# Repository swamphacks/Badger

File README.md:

# Badger

## QR Code Labels

### Installation

This script requires that Python library `qrcode` and [LibreOffice](https://www.libreoffice.org/download) be installed.

```bash
pip install -r requirements.txt
```

### Usage

Run `python cycle.py` to generate pages of QR codes. Exported PDFs will be saved in `output/`.

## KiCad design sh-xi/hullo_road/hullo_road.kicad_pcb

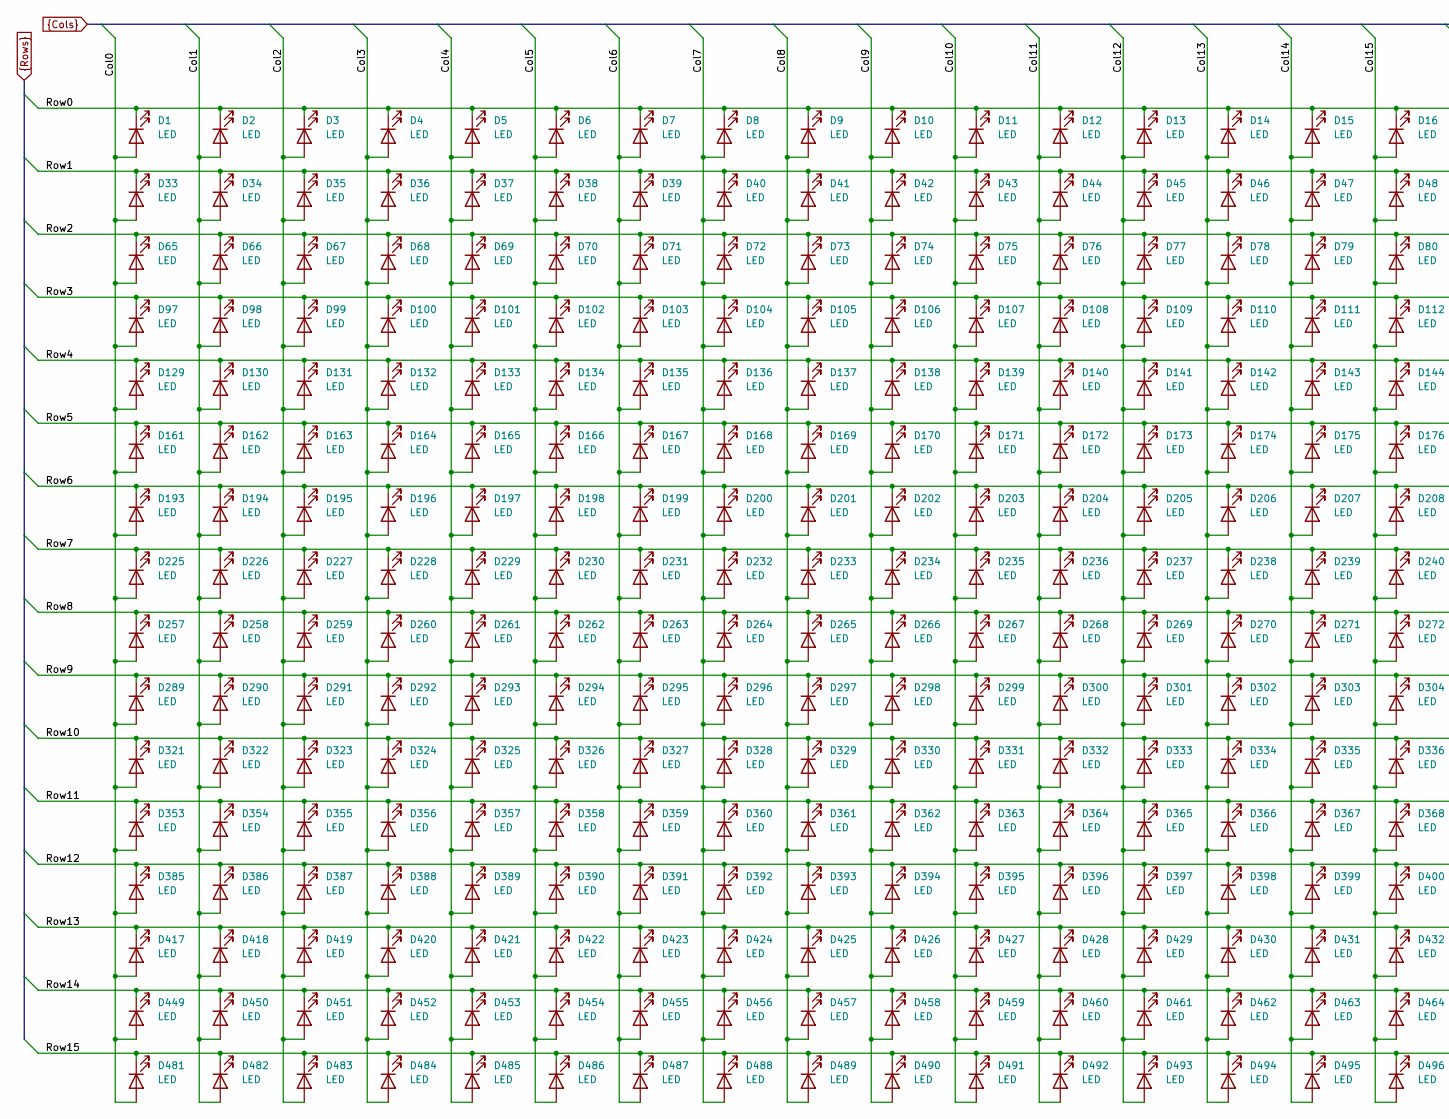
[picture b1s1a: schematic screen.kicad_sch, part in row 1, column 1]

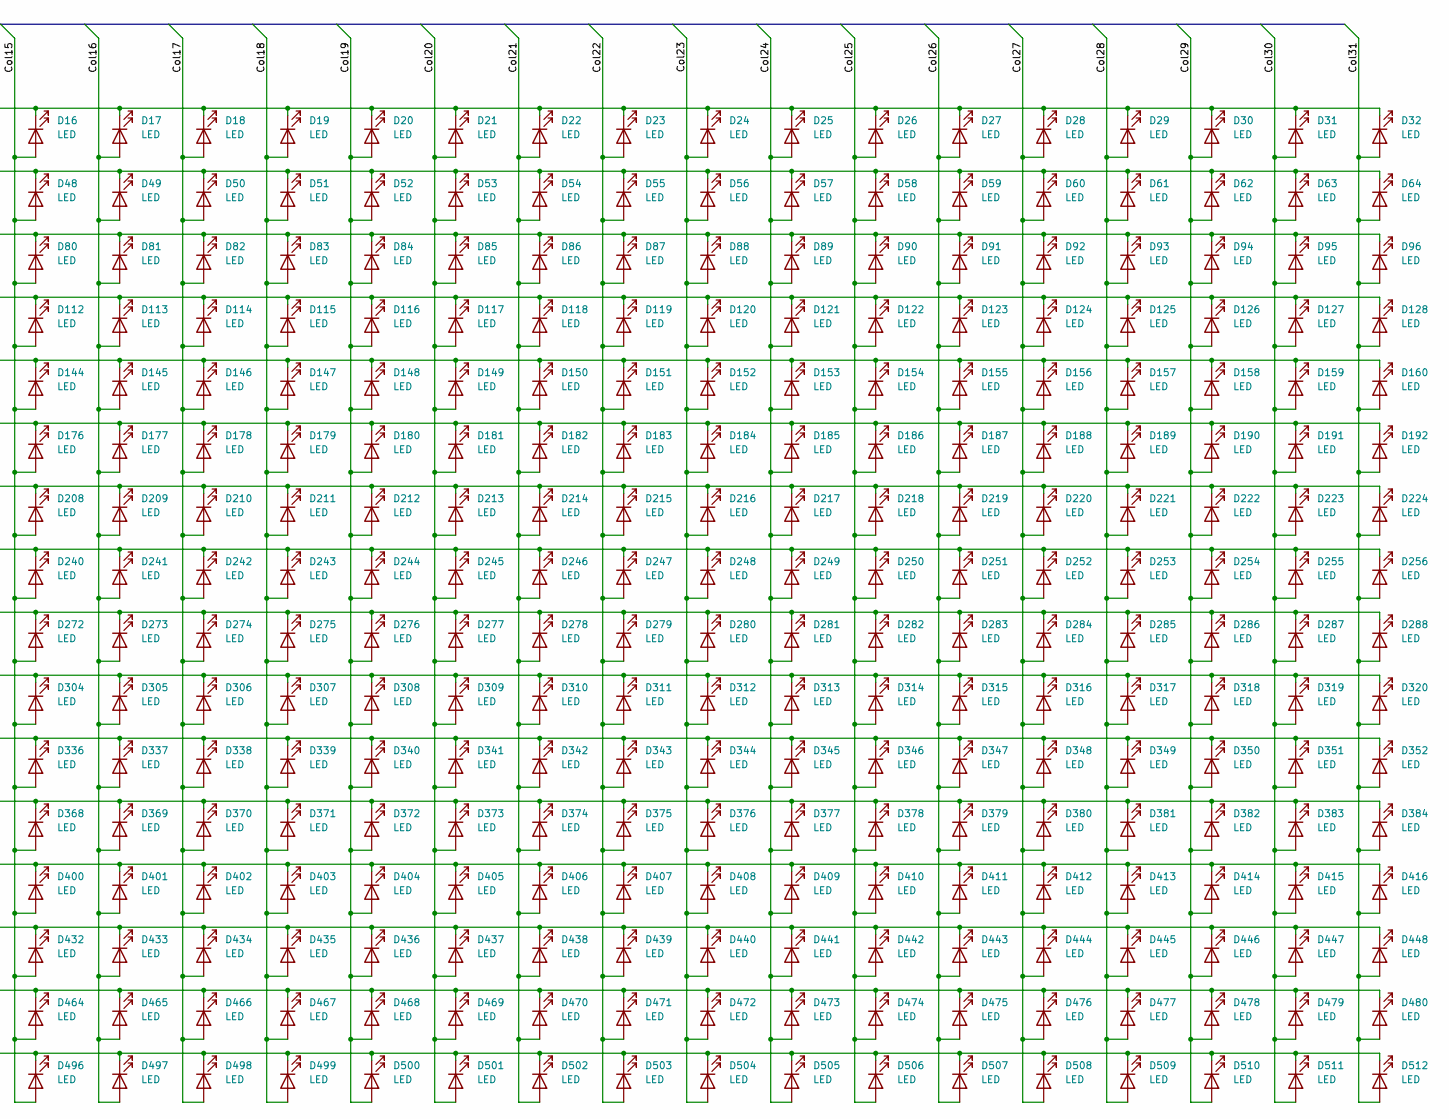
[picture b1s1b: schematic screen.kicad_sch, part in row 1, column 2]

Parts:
D1, D2, D3, D4, D5, D6, D7, D8, D9, D10, D11, D12, D13, D14, D15, D16, D17, D18, D19, D20, D21, D22, D23, D24, D25, D26, D27, D28, D29, D30, D31, D32, D33, D34, D35, D36, D37, D38, D39, D40, D41, D42, D43, D44, D45, D46, D47, D48, D49, D50, D51, D52, D53, D54, D55, D56, D57, D58, D59, D60, D61, D62, D63, D64, D65, D66, D67, D68, D69, D70, D71, D72, D73, D74, D75, D76, D77, D78, D79, D80, D81, D82, D83, D84, D85, D86, D87, D88, D89, D90, D91, D92, D93, D94, D95, D96, D97, D98, D99, D100, D101, D102, D103, D104, D105, D106, D107, D108, D109, D110, D111, D112, D113, D114, D115, D116, D117, D118, D119, D120, D121, D122, D123, D124, D125, D126, D127, D128, D129, D130, D131, D132, D133, D134, D135, D136, D137, D138, D139, D140, D141, D142, D143, D144, D145, D146, D147, D148, D149, D150, D151, D152, D153, D154, D155, D156, D157, D158, D159, D160, D161, D162, D163, D164, D165, D166, D167, D168, D169, D170, D171, D172, D173, D174, D175, D176, D177, D178, D179, D180, D181, D182, D183, D184, D185, D186, D187, D188, D189, D190, D191, D192, D193, D194, D195, D196, D197, D198, D199, D200, D201, D202, D203, D204, D205, D206, D207, D208, D209, D210, D211, D212, D213, D214, D215, D216, D217, D218, D219, D220, D221, D222, D223, D224, D225, D226, D227, D228, D229, D230, D231, D232, D233, D234, D235, D236, D237, D238, D239, D240, D241, D242, D243, D244, D245, D246, D247, D248, D249, D250, D251, D252, D253, D254, D255, D256, D257, D258, D259, D260, D261, D262, D263, D264, D265, D266, D267, D268, D269, D270, D271, D272, D273, D274, D275, D276, D277, D278, D279, D280, D281, D282, D283, D284, D285, D286, D287, D288, D289, D290, D291, D292, D293, D294, D295, D296, D297, D298, D299, D300, D301, D302, D303, D304, D305, D306, D307, D308, D309, D310, D311, D312, D313, D314, D315, D316, D317, D318, D319, D320, D321, D322, D323, D324, D325, D326, D327, D328, D329, D330, D331, D332, D333, D334, D335, D336, D337, D338, D339, D340, D341, D342, D343, D344, D345, D346, D347, D348, D349, D350, D351, D352, D353, D354, D355, D356, D357, D358, D359, D360, D361, D362, D363, D364, D365, D366, D367, D368, D369, D370, D371, D372, D373, D374, D375, D376, D377, D378, D379, D380, D381, D382, D383, D384, D385, D386, D387, D388, D389, D390, D391, D392, D393, D394, D395, D396, D397, D398, D399, D400, D401, D402, D403, D404, D405, D406, D407, D408, D409, D410, D411, D412, D413, D414, D415, D416, D417, D418, D419, D420, D421, D422, D423, D424, D425, D426, D427, D428, D429, D430, D431, D432, D433, D434, D435, D436, D437, D438, D439, D440, D441, D442, D443, D444, D445, D446, D447, D448, D449, D450, D451, D452, D453, D454, D455, D456, D457, D458, D459, D460, D461, D462, D463, D464, D465, D466, D467, D468, D469, D470, D471, D472, D473, D474, D475, D476, D477, D478, D479, D480, D481, D482, D483, D484, D485, D486, D487, D488, D489, D490, D491, D492, D493, D494, D495, D496, D497, D498, D499, D500, D501, D502, D503, D504, D505, D506, D507, D508, D509, D510, D511, D512: LED; LED_0603_1608Metric

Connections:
Col0: D1.2 (A), D33.2 (A), D65.2 (A), D97.2 (A), D129.2 (A), D161.2 (A), D193.2 (A), D225.2 (A), D257.2 (A), D289.2 (A), D321.2 (A), D353.2 (A), D385.2 (A), D417.2 (A), D449.2 (A), D481.2 (A); also elsewhere on the board
Col1: D2.2 (A), D34.2 (A), D66.2 (A), D98.2 (A), D130.2 (A), D162.2 (A), D194.2 (A), D226.2 (A), D258.2 (A), D290.2 (A), D322.2 (A), D354.2 (A), D386.2 (A), D418.2 (A), D450.2 (A), D482.2 (A); also elsewhere on the board
Col2: D3.2 (A), D35.2 (A), D67.2 (A), D99.2 (A), D131.2 (A), D163.2 (A), D195.2 (A), D227.2 (A), D259.2 (A), D291.2 (A), D323.2 (A), D355.2 (A), D387.2 (A), D419.2 (A), D451.2 (A), D483.2 (A); also elsewhere on the board
Col3: D4.2 (A), D36.2 (A), D68.2 (A), D100.2 (A), D132.2 (A), D164.2 (A), D196.2 (A), D228.2 (A), D260.2 (A), D292.2 (A), D324.2 (A), D356.2 (A), D388.2 (A), D420.2 (A), D452.2 (A), D484.2 (A); also elsewhere on the board
Col4: D5.2 (A), D37.2 (A), D69.2 (A), D101.2 (A), D133.2 (A), D165.2 (A), D197.2 (A), D229.2 (A), D261.2 (A), D293.2 (A), D325.2 (A), D357.2 (A), D389.2 (A), D421.2 (A), D453.2 (A), D485.2 (A); also elsewhere on the board
Col5: D6.2 (A), D38.2 (A), D70.2 (A), D102.2 (A), D134.2 (A), D166.2 (A), D198.2 (A), D230.2 (A), D262.2 (A), D294.2 (A), D326.2 (A), D358.2 (A), D390.2 (A), D422.2 (A), D454.2 (A), D486.2 (A); also elsewhere on the board
Col6: D7.2 (A), D39.2 (A), D71.2 (A), D103.2 (A), D135.2 (A), D167.2 (A), D199.2 (A), D231.2 (A), D263.2 (A), D295.2 (A), D327.2 (A), D359.2 (A), D391.2 (A), D423.2 (A), D455.2 (A), D487.2 (A); also elsewhere on the board
Col7: D8.2 (A), D40.2 (A), D72.2 (A), D104.2 (A), D136.2 (A), D168.2 (A), D200.2 (A), D232.2 (A), D264.2 (A), D296.2 (A), D328.2 (A), D360.2 (A), D392.2 (A), D424.2 (A), D456.2 (A), D488.2 (A); also elsewhere on the board
Col8: D9.2 (A), D41.2 (A), D73.2 (A), D105.2 (A), D137.2 (A), D169.2 (A), D201.2 (A), D233.2 (A), D265.2 (A), D297.2 (A), D329.2 (A), D361.2 (A), D393.2 (A), D425.2 (A), D457.2 (A), D489.2 (A); also elsewhere on the board
Col9: D10.2 (A), D42.2 (A), D74.2 (A), D106.2 (A), D138.2 (A), D170.2 (A), D202.2 (A), D234.2 (A), D266.2 (A), D298.2 (A), D330.2 (A), D362.2 (A), D394.2 (A), D426.2 (A), D458.2 (A), D490.2 (A); also elsewhere on the board
Col10: D11.2 (A), D43.2 (A), D75.2 (A), D107.2 (A), D139.2 (A), D171.2 (A), D203.2 (A), D235.2 (A), D267.2 (A), D299.2 (A), D331.2 (A), D363.2 (A), D395.2 (A), D427.2 (A), D459.2 (A), D491.2 (A); also elsewhere on the board
Col11: D12.2 (A), D44.2 (A), D76.2 (A), D108.2 (A), D140.2 (A), D172.2 (A), D204.2 (A), D236.2 (A), D268.2 (A), D300.2 (A), D332.2 (A), D364.2 (A), D396.2 (A), D428.2 (A), D460.2 (A), D492.2 (A); also elsewhere on the board
Col12: D13.2 (A), D45.2 (A), D77.2 (A), D109.2 (A), D141.2 (A), D173.2 (A), D205.2 (A), D237.2 (A), D269.2 (A), D301.2 (A), D333.2 (A), D365.2 (A), D397.2 (A), D429.2 (A), D461.2 (A), D493.2 (A); also elsewhere on the board
Col13: D14.2 (A), D46.2 (A), D78.2 (A), D110.2 (A), D142.2 (A), D174.2 (A), D206.2 (A), D238.2 (A), D270.2 (A), D302.2 (A), D334.2 (A), D366.2 (A), D398.2 (A), D430.2 (A), D462.2 (A), D494.2 (A); also elsewhere on the board
Col14: D15.2 (A), D47.2 (A), D79.2 (A), D111.2 (A), D143.2 (A), D175.2 (A), D207.2 (A), D239.2 (A), D271.2 (A), D303.2 (A), D335.2 (A), D367.2 (A), D399.2 (A), D431.2 (A), D463.2 (A), D495.2 (A); also elsewhere on the board
Col15: D16.2 (A), D48.2 (A), D80.2 (A), D112.2 (A), D144.2 (A), D176.2 (A), D208.2 (A), D240.2 (A), D272.2 (A), D304.2 (A), D336.2 (A), D368.2 (A), D400.2 (A), D432.2 (A), D464.2 (A), D496.2 (A); also elsewhere on the board
Col16: D17.2 (A), D49.2 (A), D81.2 (A), D113.2 (A), D145.2 (A), D177.2 (A), D209.2 (A), D241.2 (A), D273.2 (A), D305.2 (A), D337.2 (A), D369.2 (A), D401.2 (A), D433.2 (A), D465.2 (A), D497.2 (A); also elsewhere on the board
Col17: D18.2 (A), D50.2 (A), D82.2 (A), D114.2 (A), D146.2 (A), D178.2 (A), D210.2 (A), D242.2 (A), D274.2 (A), D306.2 (A), D338.2 (A), D370.2 (A), D402.2 (A), D434.2 (A), D466.2 (A), D498.2 (A); also elsewhere on the board
Col18: D19.2 (A), D51.2 (A), D83.2 (A), D115.2 (A), D147.2 (A), D179.2 (A), D211.2 (A), D243.2 (A), D275.2 (A), D307.2 (A), D339.2 (A), D371.2 (A), D403.2 (A), D435.2 (A), D467.2 (A), D499.2 (A); also elsewhere on the board
Col19: D20.2 (A), D52.2 (A), D84.2 (A), D116.2 (A), D148.2 (A), D180.2 (A), D212.2 (A), D244.2 (A), D276.2 (A), D308.2 (A), D340.2 (A), D372.2 (A), D404.2 (A), D436.2 (A), D468.2 (A), D500.2 (A); also elsewhere on the board
Col20: D21.2 (A), D53.2 (A), D85.2 (A), D117.2 (A), D149.2 (A), D181.2 (A), D213.2 (A), D245.2 (A), D277.2 (A), D309.2 (A), D341.2 (A), D373.2 (A), D405.2 (A), D437.2 (A), D469.2 (A), D501.2 (A); also elsewhere on the board
Col21: D22.2 (A), D54.2 (A), D86.2 (A), D118.2 (A), D150.2 (A), D182.2 (A), D214.2 (A), D246.2 (A), D278.2 (A), D310.2 (A), D342.2 (A), D374.2 (A), D406.2 (A), D438.2 (A), D470.2 (A), D502.2 (A); also elsewhere on the board
Col22: D23.2 (A), D55.2 (A), D87.2 (A), D119.2 (A), D151.2 (A), D183.2 (A), D215.2 (A), D247.2 (A), D279.2 (A), D311.2 (A), D343.2 (A), D375.2 (A), D407.2 (A), D439.2 (A), D471.2 (A), D503.2 (A); also elsewhere on the board
Col23: D24.2 (A), D56.2 (A), D88.2 (A), D120.2 (A), D152.2 (A), D184.2 (A), D216.2 (A), D248.2 (A), D280.2 (A), D312.2 (A), D344.2 (A), D376.2 (A), D408.2 (A), D440.2 (A), D472.2 (A), D504.2 (A); also elsewhere on the board
Col24: D25.2 (A), D57.2 (A), D89.2 (A), D121.2 (A), D153.2 (A), D185.2 (A), D217.2 (A), D249.2 (A), D281.2 (A), D313.2 (A), D345.2 (A), D377.2 (A), D409.2 (A), D441.2 (A), D473.2 (A), D505.2 (A); also elsewhere on the board
Col25: D26.2 (A), D58.2 (A), D90.2 (A), D122.2 (A), D154.2 (A), D186.2 (A), D218.2 (A), D250.2 (A), D282.2 (A), D314.2 (A), D346.2 (A), D378.2 (A), D410.2 (A), D442.2 (A), D474.2 (A), D506.2 (A); also elsewhere on the board
Col26: D27.2 (A), D59.2 (A), D91.2 (A), D123.2 (A), D155.2 (A), D187.2 (A), D219.2 (A), D251.2 (A), D283.2 (A), D315.2 (A), D347.2 (A), D379.2 (A), D411.2 (A), D443.2 (A), D475.2 (A), D507.2 (A); also elsewhere on the board
Col27: D28.2 (A), D60.2 (A), D92.2 (A), D124.2 (A), D156.2 (A), D188.2 (A), D220.2 (A), D252.2 (A), D284.2 (A), D316.2 (A), D348.2 (A), D380.2 (A), D412.2 (A), D444.2 (A), D476.2 (A), D508.2 (A); also elsewhere on the board
Col28: D29.2 (A), D61.2 (A), D93.2 (A), D125.2 (A), D157.2 (A), D189.2 (A), D221.2 (A), D253.2 (A), D285.2 (A), D317.2 (A), D349.2 (A), D381.2 (A), D413.2 (A), D445.2 (A), D477.2 (A), D509.2 (A); also elsewhere on the board
Col29: D30.2 (A), D62.2 (A), D94.2 (A), D126.2 (A), D158.2 (A), D190.2 (A), D222.2 (A), D254.2 (A), D286.2 (A), D318.2 (A), D350.2 (A), D382.2 (A), D414.2 (A), D446.2 (A), D478.2 (A), D510.2 (A); also elsewhere on the board
Col30: D31.2 (A), D63.2 (A), D95.2 (A), D127.2 (A), D159.2 (A), D191.2 (A), D223.2 (A), D255.2 (A), D287.2 (A), D319.2 (A), D351.2 (A), D383.2 (A), D415.2 (A), D447.2 (A), D479.2 (A), D511.2 (A); also elsewhere on the board
Col31: D32.2 (A), D64.2 (A), D96.2 (A), D128.2 (A), D160.2 (A), D192.2 (A), D224.2 (A), D256.2 (A), D288.2 (A), D320.2 (A), D352.2 (A), D384.2 (A), D416.2 (A), D448.2 (A), D480.2 (A), D512.2 (A); also elsewhere on the board
Row0: D1.1 (K), D2.1 (K), D3.1 (K), D4.1 (K), D5.1 (K), D6.1 (K), D7.1 (K), D8.1 (K), D9.1 (K), D10.1 (K), D11.1 (K), D12.1 (K), D13.1 (K), D14.1 (K), D15.1 (K), D16.1 (K), D17.1 (K), D18.1 (K), D19.1 (K), D20.1 (K), D21.1 (K), D22.1 (K), D23.1 (K), D24.1 (K), D25.1 (K), D26.1 (K), D27.1 (K), D28.1 (K), D29.1 (K), D30.1 (K), D31.1 (K), D32.1 (K); also elsewhere on the board
Row1: D33.1 (K), D34.1 (K), D35.1 (K), D36.1 (K), D37.1 (K), D38.1 (K), D39.1 (K), D40.1 (K), D41.1 (K), D42.1 (K), D43.1 (K), D44.1 (K), D45.1 (K), D46.1 (K), D47.1 (K), D48.1 (K), D49.1 (K), D50.1 (K), D51.1 (K), D52.1 (K), D53.1 (K), D54.1 (K), D55.1 (K), D56.1 (K), D57.1 (K), D58.1 (K), D59.1 (K), D60.1 (K), D61.1 (K), D62.1 (K), D63.1 (K), D64.1 (K); also elsewhere on the board
Row2: D65.1 (K), D66.1 (K), D67.1 (K), D68.1 (K), D69.1 (K), D70.1 (K), D71.1 (K), D72.1 (K), D73.1 (K), D74.1 (K), D75.1 (K), D76.1 (K), D77.1 (K), D78.1 (K), D79.1 (K), D80.1 (K), D81.1 (K), D82.1 (K), D83.1 (K), D84.1 (K), D85.1 (K), D86.1 (K), D87.1 (K), D88.1 (K), D89.1 (K), D90.1 (K), D91.1 (K), D92.1 (K), D93.1 (K), D94.1 (K), D95.1 (K), D96.1 (K); also elsewhere on the board
Row3: D97.1 (K), D98.1 (K), D99.1 (K), D100.1 (K), D101.1 (K), D102.1 (K), D103.1 (K), D104.1 (K), D105.1 (K), D106.1 (K), D107.1 (K), D108.1 (K), D109.1 (K), D110.1 (K), D111.1 (K), D112.1 (K), D113.1 (K), D114.1 (K), D115.1 (K), D116.1 (K), D117.1 (K), D118.1 (K), D119.1 (K), D120.1 (K), D121.1 (K), D122.1 (K), D123.1 (K), D124.1 (K), D125.1 (K), D126.1 (K), D127.1 (K), D128.1 (K); also elsewhere on the board
Row4: D129.1 (K), D130.1 (K), D131.1 (K), D132.1 (K), D133.1 (K), D134.1 (K), D135.1 (K), D136.1 (K), D137.1 (K), D138.1 (K), D139.1 (K), D140.1 (K), D141.1 (K), D142.1 (K), D143.1 (K), D144.1 (K), D145.1 (K), D146.1 (K), D147.1 (K), D148.1 (K), D149.1 (K), D150.1 (K), D151.1 (K), D152.1 (K), D153.1 (K), D154.1 (K), D155.1 (K), D156.1 (K), D157.1 (K), D158.1 (K), D159.1 (K), D160.1 (K); also elsewhere on the board
Row5: D161.1 (K), D162.1 (K), D163.1 (K), D164.1 (K), D165.1 (K), D166.1 (K), D167.1 (K), D168.1 (K), D169.1 (K), D170.1 (K), D171.1 (K), D172.1 (K), D173.1 (K), D174.1 (K), D175.1 (K), D176.1 (K), D177.1 (K), D178.1 (K), D179.1 (K), D180.1 (K), D181.1 (K), D182.1 (K), D183.1 (K), D184.1 (K), D185.1 (K), D186.1 (K), D187.1 (K), D188.1 (K), D189.1 (K), D190.1 (K), D191.1 (K), D192.1 (K); also elsewhere on the board
Row6: D193.1 (K), D194.1 (K), D195.1 (K), D196.1 (K), D197.1 (K), D198.1 (K), D199.1 (K), D200.1 (K), D201.1 (K), D202.1 (K), D203.1 (K), D204.1 (K), D205.1 (K), D206.1 (K), D207.1 (K), D208.1 (K), D209.1 (K), D210.1 (K), D211.1 (K), D212.1 (K), D213.1 (K), D214.1 (K), D215.1 (K), D216.1 (K), D217.1 (K), D218.1 (K), D219.1 (K), D220.1 (K), D221.1 (K), D222.1 (K), D223.1 (K), D224.1 (K); also elsewhere on the board
Row7: D225.1 (K), D226.1 (K), D227.1 (K), D228.1 (K), D229.1 (K), D230.1 (K), D231.1 (K), D232.1 (K), D233.1 (K), D234.1 (K), D235.1 (K), D236.1 (K), D237.1 (K), D238.1 (K), D239.1 (K), D240.1 (K), D241.1 (K), D242.1 (K), D243.1 (K), D244.1 (K), D245.1 (K), D246.1 (K), D247.1 (K), D248.1 (K), D249.1 (K), D250.1 (K), D251.1 (K), D252.1 (K), D253.1 (K), D254.1 (K), D255.1 (K), D256.1 (K); also elsewhere on the board
Row8: D257.1 (K), D258.1 (K), D259.1 (K), D260.1 (K), D261.1 (K), D262.1 (K), D263.1 (K), D264.1 (K), D265.1 (K), D266.1 (K), D267.1 (K), D268.1 (K), D269.1 (K), D270.1 (K), D271.1 (K), D272.1 (K), D273.1 (K), D274.1 (K), D275.1 (K), D276.1 (K), D277.1 (K), D278.1 (K), D279.1 (K), D280.1 (K), D281.1 (K), D282.1 (K), D283.1 (K), D284.1 (K), D285.1 (K), D286.1 (K), D287.1 (K), D288.1 (K); also elsewhere on the board
Row9: D289.1 (K), D290.1 (K), D291.1 (K), D292.1 (K), D293.1 (K), D294.1 (K), D295.1 (K), D296.1 (K), D297.1 (K), D298.1 (K), D299.1 (K), D300.1 (K), D301.1 (K), D302.1 (K), D303.1 (K), D304.1 (K), D305.1 (K), D306.1 (K), D307.1 (K), D308.1 (K), D309.1 (K), D310.1 (K), D311.1 (K), D312.1 (K), D313.1 (K), D314.1 (K), D315.1 (K), D316.1 (K), D317.1 (K), D318.1 (K), D319.1 (K), D320.1 (K); also elsewhere on the board
Row10: D321.1 (K), D322.1 (K), D323.1 (K), D324.1 (K), D325.1 (K), D326.1 (K), D327.1 (K), D328.1 (K), D329.1 (K), D330.1 (K), D331.1 (K), D332.1 (K), D333.1 (K), D334.1 (K), D335.1 (K), D336.1 (K), D337.1 (K), D338.1 (K), D339.1 (K), D340.1 (K), D341.1 (K), D342.1 (K), D343.1 (K), D344.1 (K), D345.1 (K), D346.1 (K), D347.1 (K), D348.1 (K), D349.1 (K), D350.1 (K), D351.1 (K), D352.1 (K); also elsewhere on the board
Row11: D353.1 (K), D354.1 (K), D355.1 (K), D356.1 (K), D357.1 (K), D358.1 (K), D359.1 (K), D360.1 (K), D361.1 (K), D362.1 (K), D363.1 (K), D364.1 (K), D365.1 (K), D366.1 (K), D367.1 (K), D368.1 (K), D369.1 (K), D370.1 (K), D371.1 (K), D372.1 (K), D373.1 (K), D374.1 (K), D375.1 (K), D376.1 (K), D377.1 (K), D378.1 (K), D379.1 (K), D380.1 (K), D381.1 (K), D382.1 (K), D383.1 (K), D384.1 (K); also elsewhere on the board
Row12: D385.1 (K), D386.1 (K), D387.1 (K), D388.1 (K), D389.1 (K), D390.1 (K), D391.1 (K), D392.1 (K), D393.1 (K), D394.1 (K), D395.1 (K), D396.1 (K), D397.1 (K), D398.1 (K), D399.1 (K), D400.1 (K), D401.1 (K), D402.1 (K), D403.1 (K), D404.1 (K), D405.1 (K), D406.1 (K), D407.1 (K), D408.1 (K), D409.1 (K), D410.1 (K), D411.1 (K), D412.1 (K), D413.1 (K), D414.1 (K), D415.1 (K), D416.1 (K); also elsewhere on the board
Row13: D417.1 (K), D418.1 (K), D419.1 (K), D420.1 (K), D421.1 (K), D422.1 (K), D423.1 (K), D424.1 (K), D425.1 (K), D426.1 (K), D427.1 (K), D428.1 (K), D429.1 (K), D430.1 (K), D431.1 (K), D432.1 (K), D433.1 (K), D434.1 (K), D435.1 (K), D436.1 (K), D437.1 (K), D438.1 (K), D439.1 (K), D440.1 (K), D441.1 (K), D442.1 (K), D443.1 (K), D444.1 (K), D445.1 (K), D446.1 (K), D447.1 (K), D448.1 (K); also elsewhere on the board
Row14: D449.1 (K), D450.1 (K), D451.1 (K), D452.1 (K), D453.1 (K), D454.1 (K), D455.1 (K), D456.1 (K), D457.1 (K), D458.1 (K), D459.1 (K), D460.1 (K), D461.1 (K), D462.1 (K), D463.1 (K), D464.1 (K), D465.1 (K), D466.1 (K), D467.1 (K), D468.1 (K), D469.1 (K), D470.1 (K), D471.1 (K), D472.1 (K), D473.1 (K), D474.1 (K), D475.1 (K), D476.1 (K), D477.1 (K), D478.1 (K), D479.1 (K), D480.1 (K); also elsewhere on the board
Row15: D481.1 (K), D482.1 (K), D483.1 (K), D484.1 (K), D485.1 (K), D486.1 (K), D487.1 (K), D488.1 (K), D489.1 (K), D490.1 (K), D491.1 (K), D492.1 (K), D493.1 (K), D494.1 (K), D495.1 (K), D496.1 (K), D497.1 (K), D498.1 (K), D499.1 (K), D500.1 (K), D501.1 (K), D502.1 (K), D503.1 (K), D504.1 (K), D505.1 (K), D506.1 (K), D507.1 (K), D508.1 (K), D509.1 (K), D510.1 (K), D511.1 (K), D512.1 (K); also elsewhere on the board

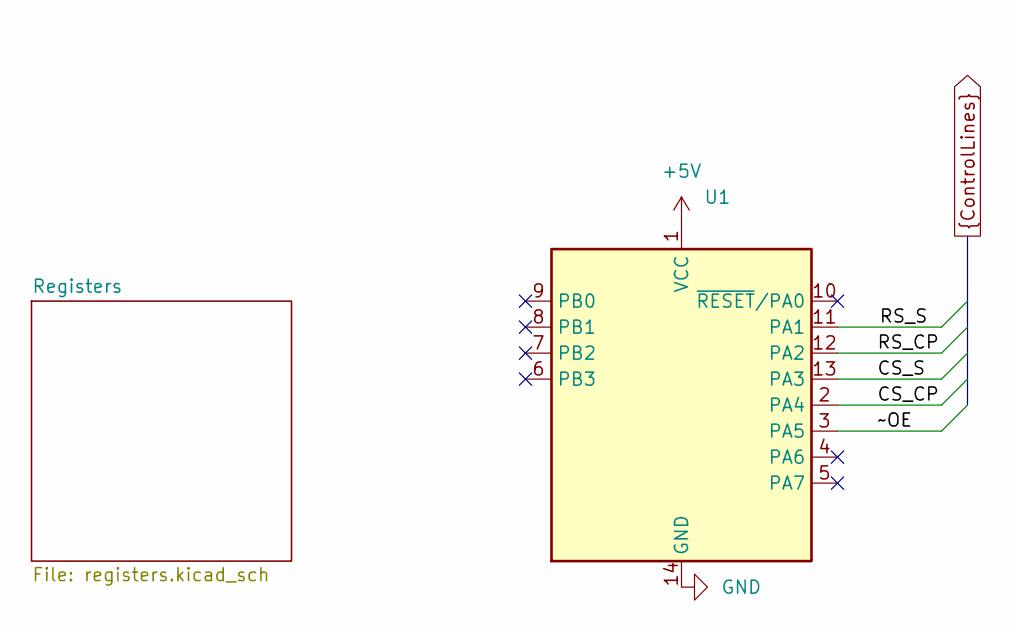
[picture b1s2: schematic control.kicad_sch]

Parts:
U1: ATtiny414-SS; SOIC-14_3.9x8.7mm_P1.27mm

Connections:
+5V: U1.1 (VCC); also elsewhere on the board
CS_CP: U1.2 (PA4); also elsewhere on the board
CS_S: U1.13 (PA3); also elsewhere on the board
GND: U1.14 (GND); also elsewhere on the board
RS_CP: U1.12 (PA2); also elsewhere on the board
RS_S: U1.11 (PA1); also elsewhere on the board
~OE: U1.3 (PA5); also elsewhere on the board

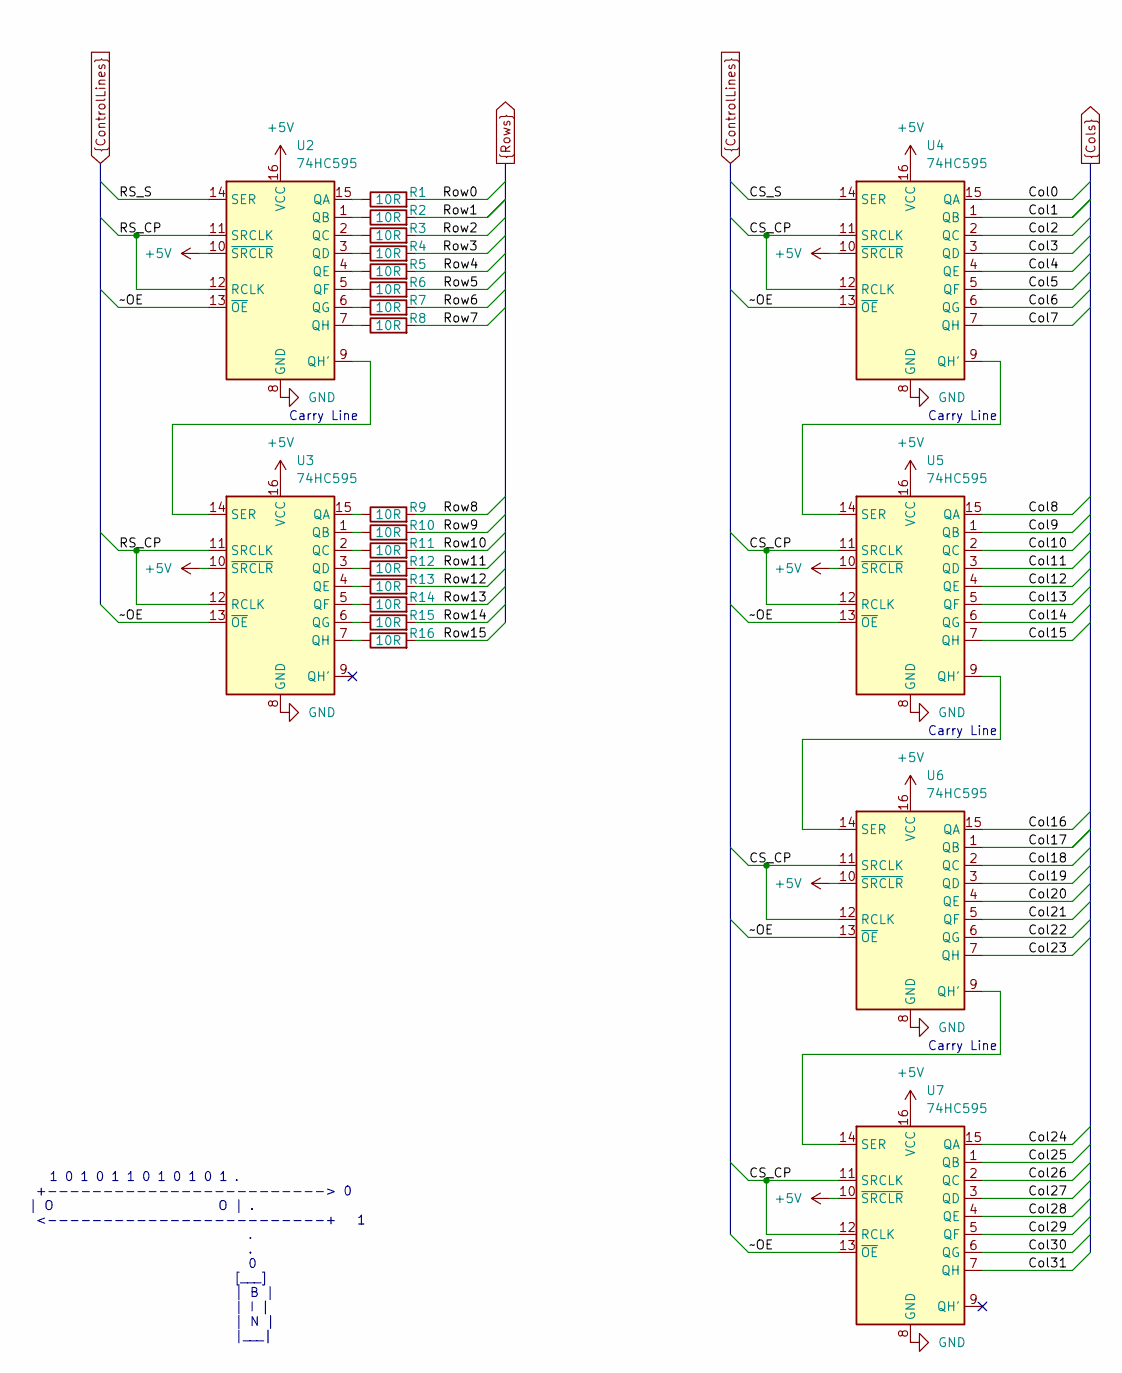
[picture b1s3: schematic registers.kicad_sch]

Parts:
R1, R2, R3, R4, R5, R6, R7, R8, R9, R10, R11, R12, R13, R14, R15, R16: 10R; R_0805_2012Metric
U2, U3, U4, U5, U6, U7: 74HC595; TSSOP-16_4.4x5mm_P0.65mm

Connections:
+5V: U2.10 (~SRCLR), U2.16 (VCC), U3.10 (~SRCLR), U3.16 (VCC), U4.10 (~SRCLR), U4.16 (VCC), U5.10 (~SRCLR), U5.16 (VCC), U6.10 (~SRCLR), U6.16 (VCC), U7.10 (~SRCLR), U7.16 (VCC); also elsewhere on the board
CS_CP: U4.11 (SRCLK), U4.12 (RCLK), U5.11 (SRCLK), U5.12 (RCLK), U6.11 (SRCLK), U6.12 (RCLK), U7.11 (SRCLK), U7.12 (RCLK); also elsewhere on the board
CS_S: U4.14 (SER); also elsewhere on the board
Col0: U4.15 (QA); also elsewhere on the board
Col1: U4.1 (QB); also elsewhere on the board
Col2: U4.2 (QC); also elsewhere on the board
Col3: U4.3 (QD); also elsewhere on the board
Col4: U4.4 (QE); also elsewhere on the board
Col5: U4.5 (QF); also elsewhere on the board
Col6: U4.6 (QG); also elsewhere on the board
Col7: U4.7 (QH); also elsewhere on the board
Col8: U5.15 (QA); also elsewhere on the board
Col9: U5.1 (QB); also elsewhere on the board
Col10: U5.2 (QC); also elsewhere on the board
Col11: U5.3 (QD); also elsewhere on the board
Col12: U5.4 (QE); also elsewhere on the board
Col13: U5.5 (QF); also elsewhere on the board
Col14: U5.6 (QG); also elsewhere on the board
Col15: U5.7 (QH); also elsewhere on the board
Col16: U6.15 (QA); also elsewhere on the board
Col17: U6.1 (QB); also elsewhere on the board
Col18: U6.2 (QC); also elsewhere on the board
Col19: U6.3 (QD); also elsewhere on the board
Col20: U6.4 (QE); also elsewhere on the board
Col21: U6.5 (QF); also elsewhere on the board
Col22: U6.6 (QG); also elsewhere on the board
Col23: U6.7 (QH); also elsewhere on the board
Col24: U7.15 (QA); also elsewhere on the board
Col25: U7.1 (QB); also elsewhere on the board
Col26: U7.2 (QC); also elsewhere on the board
Col27: U7.3 (QD); also elsewhere on the board
Col28: U7.4 (QE); also elsewhere on the board
Col29: U7.5 (QF); also elsewhere on the board
Col30: U7.6 (QG); also elsewhere on the board
Col31: U7.7 (QH); also elsewhere on the board
GND: U2.8 (GND), U3.8 (GND), U4.8 (GND), U5.8 (GND), U6.8 (GND), U7.8 (GND); also elsewhere on the board
unnamed: R1.1, U2.15 (QA)
unnamed: R2.1, U2.1 (QB)
unnamed: R3.1, U2.2 (QC)
unnamed: R4.1, U2.3 (QD)
unnamed: R5.1, U2.4 (QE)
unnamed: R6.1, U2.5 (QF)
unnamed: R7.1, U2.6 (QG)
unnamed: U2.9 (QH'), U3.14 (SER)
unnamed: R8.1, U2.7 (QH)
unnamed: R9.1, U3.15 (QA)
unnamed: R10.1, U3.1 (QB)
unnamed: R11.1, U3.2 (QC)
unnamed: R12.1, U3.3 (QD)
unnamed: R13.1, U3.4 (QE)
unnamed: R14.1, U3.5 (QF)
unnamed: R15.1, U3.6 (QG)
unnamed: R16.1, U3.7 (QH)
unnamed: U4.9 (QH'), U5.14 (SER)
unnamed: U5.9 (QH'), U6.14 (SER)
unnamed: U6.9 (QH'), U7.14 (SER)
RS_CP: U2.11 (SRCLK), U2.12 (RCLK), U3.11 (SRCLK), U3.12 (RCLK); also elsewhere on the board
RS_S: U2.14 (SER); also elsewhere on the board
Row0: R1.2; also elsewhere on the board
Row1: R2.2; also elsewhere on the board
Row2: R3.2; also elsewhere on the board
Row3: R4.2; also elsewhere on the board
Row4: R5.2; also elsewhere on the board
Row5: R6.2; also elsewhere on the board
Row6: R7.2; also elsewhere on the board
Row7: R8.2; also elsewhere on the board
Row8: R9.2; also elsewhere on the board
Row9: R10.2; also elsewhere on the board
Row10: R11.2; also elsewhere on the board
Row11: R12.2; also elsewhere on the board
Row12: R13.2; also elsewhere on the board
Row13: R14.2; also elsewhere on the board
Row14: R15.2; also elsewhere on the board
Row15: R16.2; also elsewhere on the board
~OE: U2.13 (~OE), U3.13 (~OE), U4.13 (~OE), U5.13 (~OE), U6.13 (~OE), U7.13 (~OE); also elsewhere on the board

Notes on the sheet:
Carry Line
1 0 1 0 1 1 0 1 0 1 0 1 . +-------------------------> 0 | O O | . <-------------------------+ 1 . . 0 [___] | B | | I | | N | |___|

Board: 2 copper layers, 535 parts (0 on the bottom side), 75 nets, no tracks yet.

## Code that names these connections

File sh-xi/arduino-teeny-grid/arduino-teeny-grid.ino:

/*
 * ATtiny414 LED Matrix - Graphic display.
 * 
 * Revision History:
 *  Oct-13  First authored by Robert Conde for SwampHack XI.
 *           Made with ❤️!
 *  Oct-14  First checkerboard on October 14th w/ Jason from
 *           Toronto.
 *  Oct-21  First graphic on October 21st (thinking of Jason
 *           from Toronto).
 * 
 * Pin Assignment:
 * - PA1: S_R   (Row data)
 * - PA2: CLK_R (Row clock)
 * - PA3: S_C   (Column data)
 * - PA4: CLK_C (Column clock)
 * - PA5: ~OE   (Output Enable - active LOW)
 * 
 */

#include <avr/io.h>
#include <util/delay.h>
#include <avr/pgmspace.h>

// Pin definitions
#define S_R_PIN     PIN1_bm    // PA1 - Row data
#define CLK_R_PIN   PIN2_bm    // PA2 - Row clock
#define S_C_PIN     PIN3_bm    // PA3 - Column data
#define CLK_C_PIN   PIN4_bm    // PA4 - Column clock
#define OE_PIN      PIN5_bm    // PA5 - Output Enable

#define ROWS 16
#define COLS 32

// Graphic pattern
// Each row is 4 bytes (32 bits), stored in program memory
const uint8_t graphic[ROWS][4] PROGMEM = {
    {0b00000000, 0b00000000, 0b00000000, 0b00000000}, // Row 00
    {0b01000001, 0b00000000, 0b00001001, 0b00111110}, // Row 01
    {0b01000001, 0b00000000, 0b00001001, 0b00111110}, // Row 02
    {0b01000001, 0b00001001, 0b00001001, 0b00111110}, // Row 03
    {0b01000001, 0b00000000, 0b00001001, 0b00011100}, // Row 04
    {0b01000001, 0b00000000, 0b00001001, 0b00011100}, // Row 05
    {0b01000001, 0b00001111, 0b00001001, 0b00011100}, // Row 06
    {0b01111111, 0b00010000, 0b10001001, 0b00001000}, // Row 07
    {0b01000001, 0b00100000, 0b01001001, 0b00001000}, // Row 08
    {0b01000001, 0b00100000, 0b01001001, 0b00000000}, // Row 09
    {0b01000001, 0b00111111, 0b10001001, 0b00011100}, // Row 10
    {0b01000001, 0b00100000, 0b00001001, 0b00101010}, // Row 11
    {0b01000001, 0b00100000, 0b00001001, 0b00110110}, // Row 12
    {0b01000001, 0b00010000, 0b00001001, 0b00101010}, // Row 13
    {0b01000001, 0b00001111, 0b10000100, 0b10011100}, // Row 14
    {0b00000000, 0b00000000, 0b00000000, 0b00000000}, // Row 15
};

// Current bit position (0-31)
uint8_t row_select = ROWS;

void init_gpio(void) {
    // Set outputs
    PORTA.DIRSET = S_R_PIN | CLK_R_PIN | S_C_PIN | CLK_C_PIN | OE_PIN;
    
    // Initialize: data HIGH, clocks LOW, OE disabled (HIGH)
    PORTA.OUTSET = S_R_PIN | S_C_PIN | OE_PIN;
    PORTA.OUTCLR = CLK_R_PIN | CLK_C_PIN;
}

// Shift out a single bit
void shift_bit(uint8_t bit, uint8_t data_pin, uint8_t clock_pin) {
    // Set data
    if (bit) {
        PORTA.OUTSET = data_pin;
    } else {
        PORTA.OUTCLR = data_pin;
    }
    
    _delay_us(1);
    
    // Clock HIGH
    PORTA.OUTSET = clock_pin;
    _delay_us(1);
    
    // Clock LOW
    PORTA.OUTCLR = clock_pin;
    _delay_us(1);
}

void reset_registers(void) {
    // Deselect all rows
    for (uint8_t i = 0; i < ROWS + 1; i++) {
        shift_bit(1, S_R_PIN, CLK_R_PIN);
    }

    // Deselect all columns
    for (uint8_t i = 0; i < COLS + 1; i++) {
        shift_bit(0, S_C_PIN, CLK_C_PIN);
    }
}

// Get pixel value from heart pattern
// Current byte and bit position for shifting
uint8_t current_byte;
uint8_t current_bit_mask;

void display_next_row(void) {
    /* Hide */
    // Disable output
    PORTA.OUTSET = OE_PIN;

    /* Select the row*/
    // Shift (perhaps in) the row select bit
    uint8_t loopback = ++row_select >= ROWS;
    shift_bit(!loopback, S_R_PIN, CLK_R_PIN);
    if (loopback) {
        shift_bit(1, S_R_PIN, CLK_R_PIN);
        row_select %= ROWS; // fix 'da counter
    }

    /* Assemble the row */
    // Load last byte and initialize bit mask (shift in reverse order)
    uint8_t byte_idx = 3;
    current_byte = pgm_read_byte(&graphic[row_select][byte_idx]);
    current_bit_mask = 0x01; // Start with LSB

    for (uint8_t i = 0; i < COLS; i++) {
        // Shift out current bit
        shift_bit(current_byte & current_bit_mask, S_C_PIN, CLK_C_PIN);
        
        // Move to next bit
        current_bit_mask <<= 1;
        
        // If we've exhausted this byte, load the previous one
        if (current_bit_mask == 0) {
            if (byte_idx > 0) {
                byte_idx--;
                current_byte = pgm_read_byte(&graphic[row_select][byte_idx]);
            }
            current_bit_mask = 0x01; // Reset to LSB
        }
    }
    
    shift_bit(0, S_C_PIN, CLK_C_PIN); // extra shift since we tied clocks together!

    /* Flash Row */
    // Enable output
    PORTA.OUTCLR = OE_PIN;
    // Wait some time...
    _delay_us(25); // Plenty of time
}

int main(void) {
    init_gpio();

    reset_registers();

    shift_bit(0, S_R_PIN, CLK_R_PIN); // TODO: consider if needed
    while (true) {
        display_next_row();
    }
    
    return 0;
}

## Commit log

2025-01-21 Eww sticky!!
2025-01-23 Batch
2025-10-12 Move old badging system
2025-10-12 Add new Rust project for SH-XI badge
2025-10-14 Basic 16x32 LED matrix driver via shift registers
2025-10-14 Checkboard! 🏁
2025-10-14 Add 8x16 PCB module
2025-10-21 Graphics!!!!
2025-10-21 Remove Rust project :(
2025-10-21 Hullo road 🚗
2025-10-31 Add LED matrix
2025-10-31 Add matrix control via shift registers and attiny414
2025-10-31 Place LEDs in a grid
2025-11-04 Create two board design and route most things
